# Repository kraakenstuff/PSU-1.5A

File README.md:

# PSU-1.5A
Small Eurorack PSU and bus board based on Meanwell RDDW20F-12

Status: tested and working.

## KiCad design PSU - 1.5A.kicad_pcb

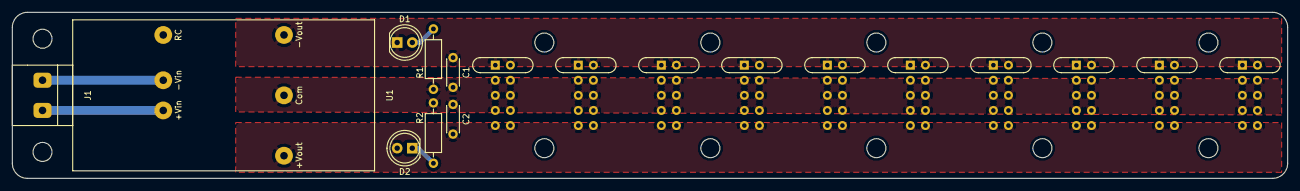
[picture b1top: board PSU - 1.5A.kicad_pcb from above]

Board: 2 copper layers, 214.6 x 27.9 mm, 8 parts (0 on the bottom side), 7 nets.

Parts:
C1, C2: 100n; C_Disc_D4.3mm_W1.9mm_P5.00mm
D1, D2: LED; LED_D5.0mm
J1: PWR_IN; Klema x2
R1, R2: 1k2; R_Axial_DIN0207_L6.3mm_D2.5mm_P10.16mm_Horizontal
U1: MeanWellRDDW20F-12; MeanWell RDDW20F

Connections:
+12V: C2.2, D2.2, U1.3
-12V: C1.1, D1.1, U1.5
GND: C1.2, C2.1, R1.2, R2.1, U1.4
unnamed: D1.2, R1.1
unnamed: D2.1, R2.2
unnamed: J1.1, U1.1
unnamed: J1.2, U1.2

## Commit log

2019-02-14 Added net file
2019-02-14 Updated Meanwell footprint
2019-03-05 Updated dc/dc adapter footprint
2019-03-05 Updated gerbers.
2019-03-05 Updated status of the project
2019-06-07 Added power bus
